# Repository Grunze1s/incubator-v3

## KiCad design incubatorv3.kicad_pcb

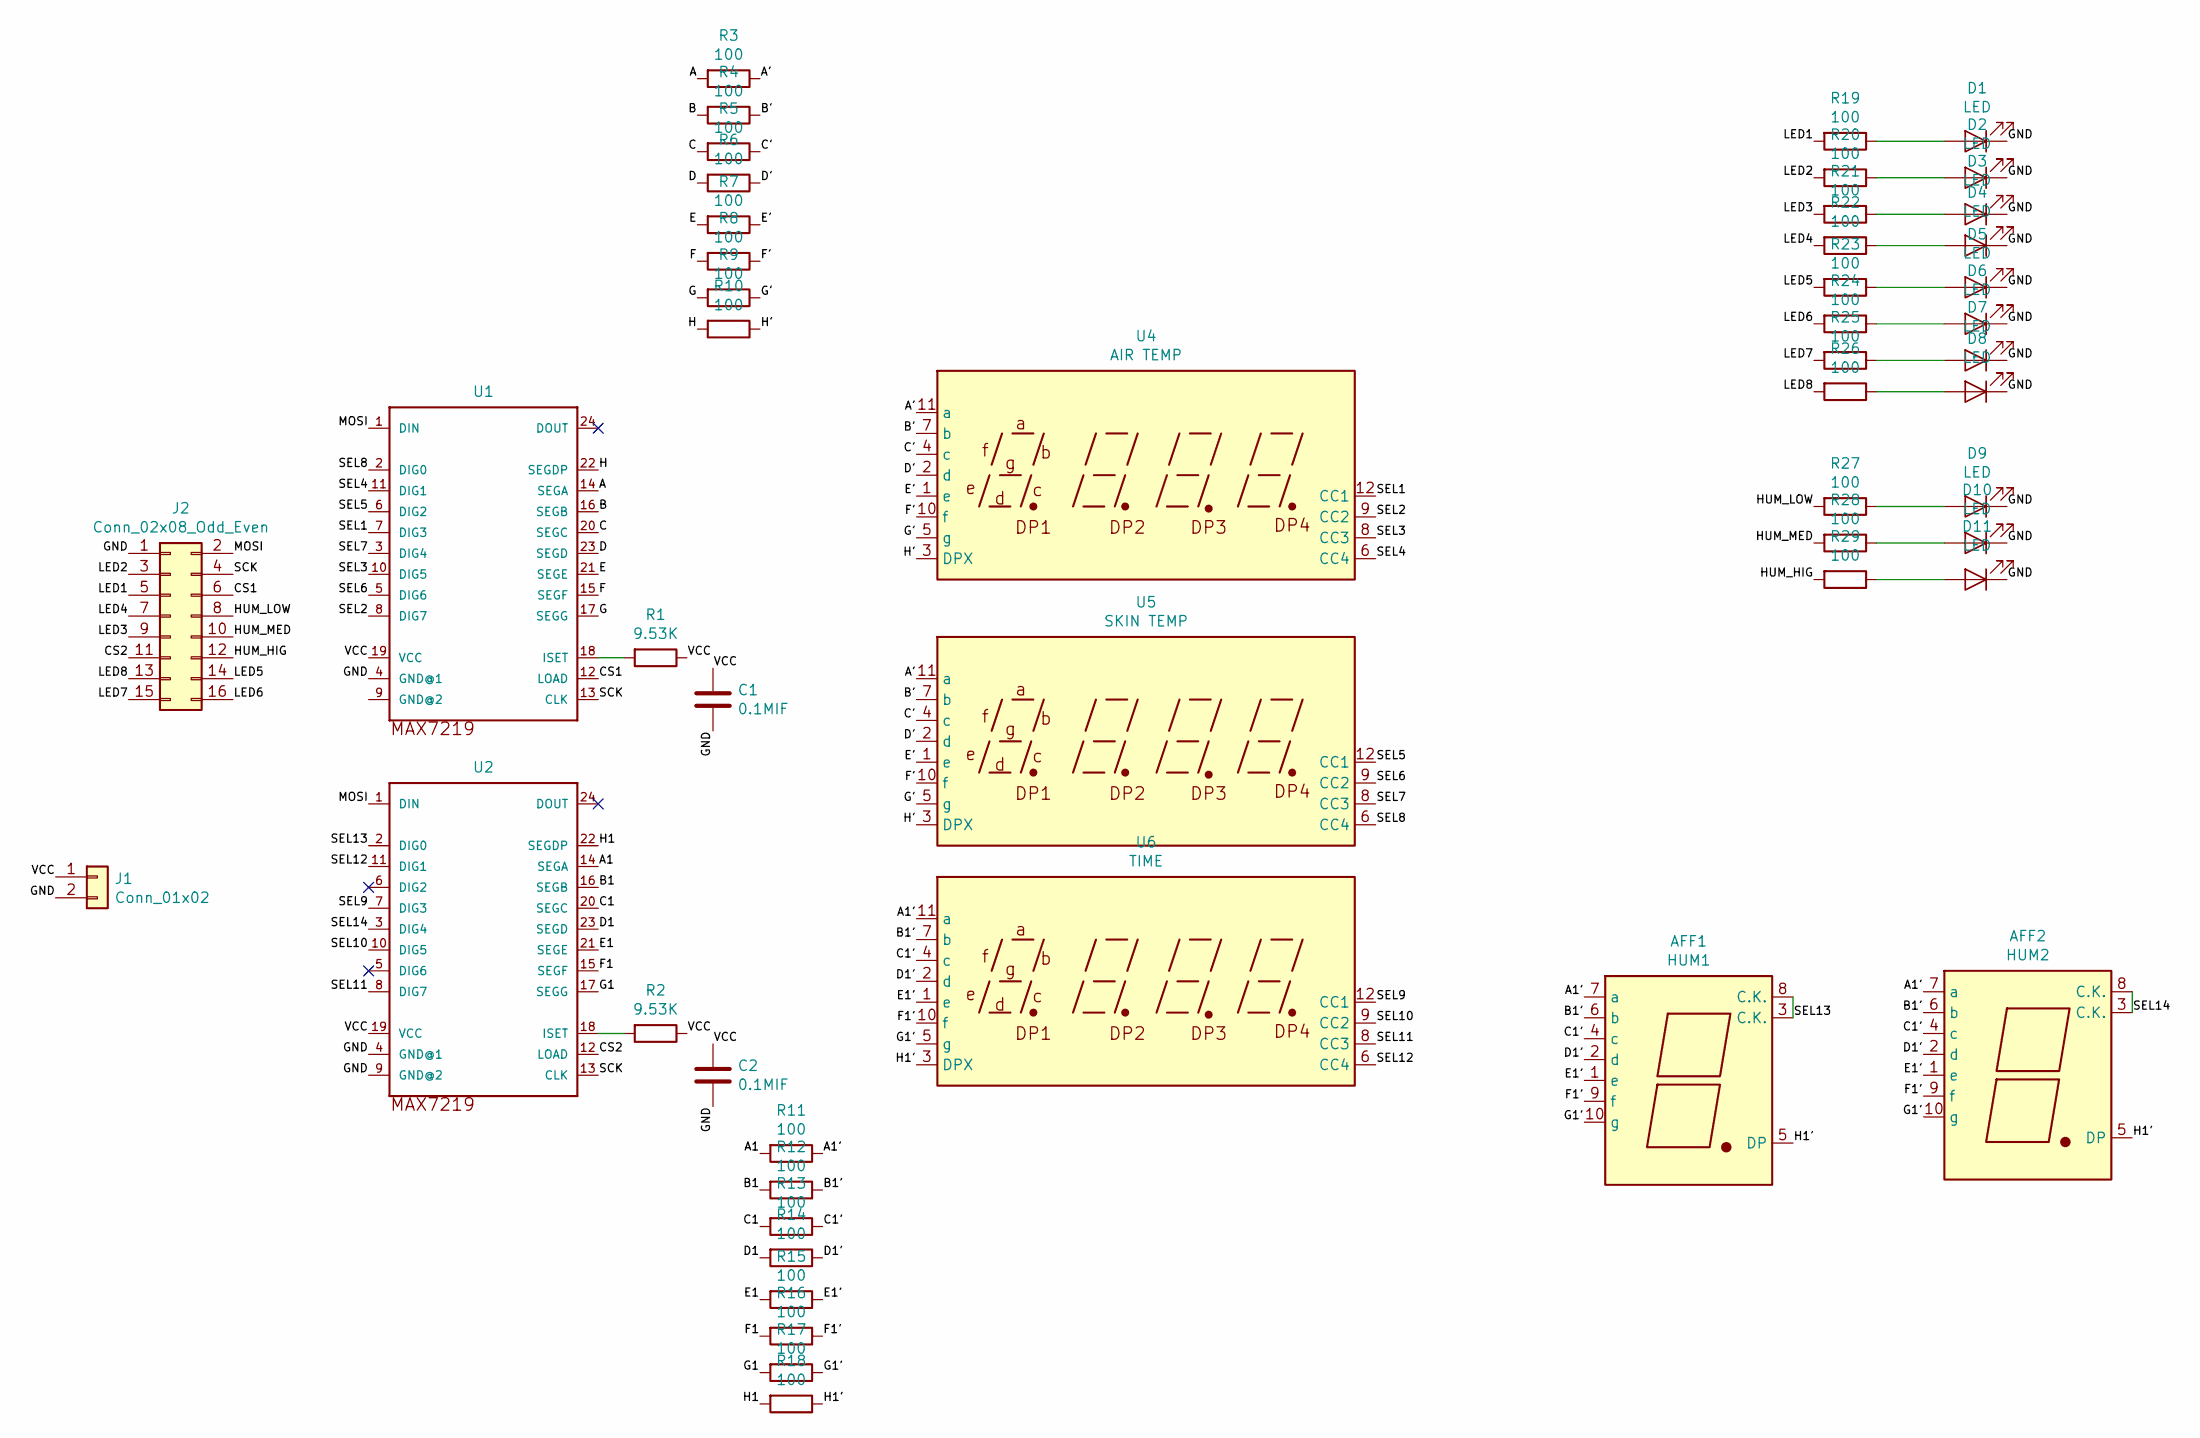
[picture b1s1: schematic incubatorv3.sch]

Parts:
AFF1: HUM1; 7SegmentLED_LTS6760_LTS6780
AFF2: HUM2; 7SegmentLED_LTS6760_LTS6780
C1, C2: 0.1MIF; C_Disc_D3.0mm_W1.6mm_P2.50mm
D1, D2, D3, D4, D5, D6, D7, D8, D9, D10, D11: LED; LED_D5.0mm
J1: Conn_01x02; PinHeader_1x02_P2.54mm_Vertical
J2: Conn_02x08_Odd_Even; PinHeader_2x08_P2.54mm_Vertical
R1, R2: 9.53K; R_Axial_DIN0204_L3.6mm_D1.6mm_P5.08mm_Horizontal
R3, R4, R5, R6, R7, R8, R9, R10, R11, R12, R13, R14, R15, R16, R17, R18, R19, R20, R21, R22, R23, R24, R25, R26, R27, R28, R29: 100; R_Axial_DIN0204_L3.6mm_D1.6mm_P5.08mm_Horizontal
U1, U2: MAX7219; DIL24
U4: AIR TEMP; CC56-12GWA
U5: SKIN TEMP; CC56-12GWA
U6: TIME; CC56-12GWA

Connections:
/A: R3.2, U1.14 (SEGA)
/A1: R11.2, U2.14 (SEGA)
/A1': AFF1.7 (a), AFF2.7 (a), R11.1, U6.11 (a)
/A': R3.1, U4.11 (a), U5.11 (a)
/B: R4.2, U1.16 (SEGB)
/B1: R12.2, U2.16 (SEGB)
/B1': AFF1.6 (b), AFF2.6 (b), R12.1, U6.7 (b)
/B': R4.1, U4.7 (b), U5.7 (b)
/C: R5.2, U1.20 (SEGC)
/C1: R13.2, U2.20 (SEGC)
/C1': AFF1.4 (c), AFF2.4 (c), R13.1, U6.4 (c)
/C': R5.1, U4.4 (c), U5.4 (c)
/CS1: J2.6, U1.12 (LOAD)
/CS2: J2.11, U2.12 (LOAD)
/D: R6.2, U1.23 (SEGD)
/D1: R14.2, U2.23 (SEGD)
/D1': AFF1.2 (d), AFF2.2 (d), R14.1, U6.2 (d)
/D': R6.1, U4.2 (d), U5.2 (d)
/E: R7.2, U1.21 (SEGE)
/E1: R15.2, U2.21 (SEGE)
/E1': AFF1.1 (e), AFF2.1 (e), R15.1, U6.1 (e)
/E': R7.1, U4.1 (e), U5.1 (e)
/F: R8.2, U1.15 (SEGF)
/F1: R16.2, U2.15 (SEGF)
/F1': AFF1.9 (f), AFF2.9 (f), R16.1, U6.10 (f)
/F': R8.1, U4.10 (f), U5.10 (f)
/G: R9.2, U1.17 (SEGG)
/G1: R17.2, U2.17 (SEGG)
/G1': AFF1.10 (g), AFF2.10 (g), R17.1, U6.5 (g)
/G': R9.1, U4.5 (g), U5.5 (g)
/GND: C1.2, C2.2, D1.1 (K), D2.1 (K), D3.1 (K), D4.1 (K), D5.1 (K), D6.1 (K), D7.1 (K), D8.1 (K), D9.1 (K), D10.1 (K), D11.1 (K), J1.2, J2.1, U1.4 (GND@1), U2.4 (GND@1), U2.9 (GND@2)
/H: R10.2, U1.22 (SEGDP)
/H1: R18.2, U2.22 (SEGDP)
/H1': AFF1.5 (DP), AFF2.5 (DP), R18.1, U6.3 (DPX)
/H': R10.1, U4.3 (DPX), U5.3 (DPX)
/HUM_HIG: J2.12, R29.2
/HUM_LOW: J2.8, R27.2
/HUM_MED: J2.10, R28.2
/LED1: J2.5, R19.2
/LED2: J2.3, R20.2
/LED3: J2.9, R21.2
/LED4: J2.7, R22.2
/LED5: J2.14, R23.2
/LED6: J2.16, R24.2
/LED7: J2.15, R25.2
/LED8: J2.13, R26.2
/MOSI: J2.2, U1.1 (DIN), U2.1 (DIN)
/SCK: J2.4, U1.13 (CLK), U2.13 (CLK)
/SEL1: U1.7 (DIG3), U4.12 (CC1)
/SEL2: U1.8 (DIG7), U4.9 (CC2)
/SEL3: U1.10 (DIG5), U4.8 (CC3)
/SEL4: U1.11 (DIG1), U4.6 (CC4)
/SEL5: U1.6 (DIG2), U5.12 (CC1)
/SEL6: U1.5 (DIG6), U5.9 (CC2)
/SEL7: U1.3 (DIG4), U5.8 (CC3)
/SEL8: U1.2 (DIG0), U5.6 (CC4)
/SEL9: U2.7 (DIG3), U6.12 (CC1)
/SEL10: U2.10 (DIG5), U6.9 (CC2)
/SEL11: U2.8 (DIG7), U6.8 (CC3)
/SEL12: U2.11 (DIG1), U6.6 (CC4)
/SEL13: AFF1.3 (C.K.), AFF1.8 (C.K.), U2.2 (DIG0)
/SEL14: AFF2.3 (C.K.), AFF2.8 (C.K.), U2.3 (DIG4)
/VCC: C1.1, C2.1, J1.1, R1.1, R2.1, U1.19 (VCC), U2.19 (VCC)
unnamed: D1.2 (A), R19.1
unnamed: D2.2 (A), R20.1
unnamed: D3.2 (A), R21.1
unnamed: D4.2 (A), R22.1
unnamed: D5.2 (A), R23.1
unnamed: D6.2 (A), R24.1
unnamed: D7.2 (A), R25.1
unnamed: D8.2 (A), R26.1
unnamed: D9.2 (A), R27.1
unnamed: D10.2 (A), R28.1
unnamed: D11.2 (A), R29.1
unnamed: R1.2, U1.18 (ISET)
unnamed: R2.2, U2.18 (ISET)

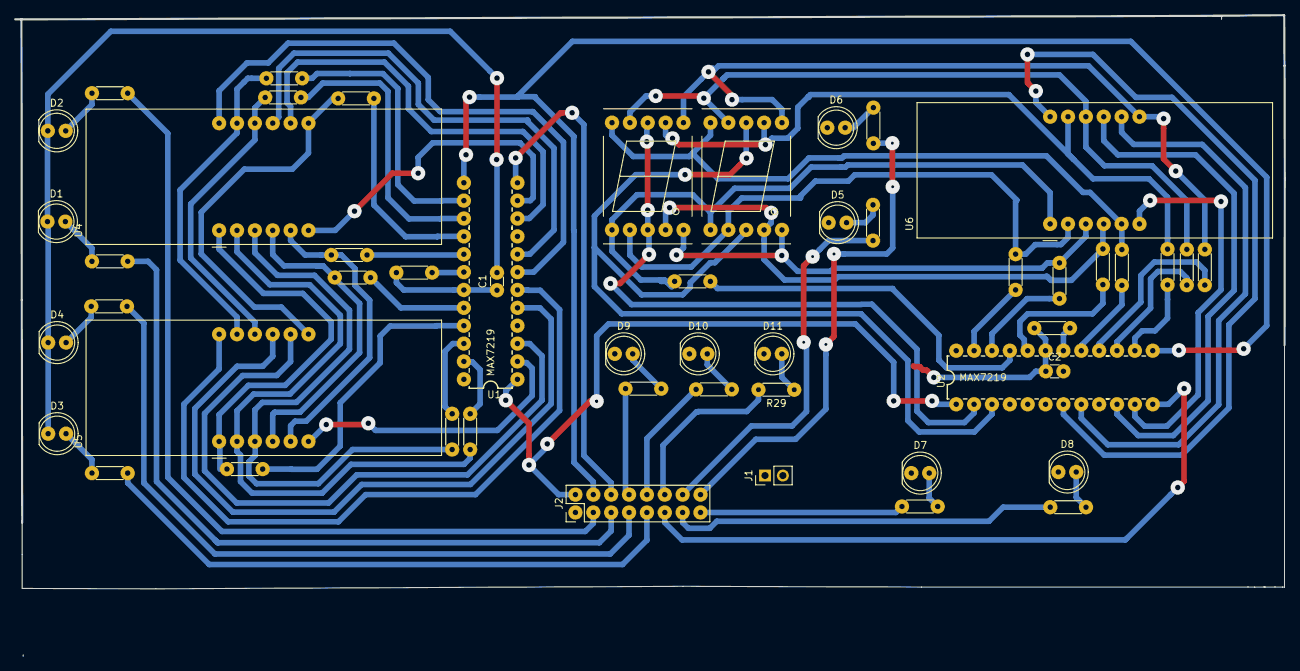
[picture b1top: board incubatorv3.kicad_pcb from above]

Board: 2 copper layers, 180.5 x 91.0 mm, 51 parts (0 on the bottom side), 76 nets.
